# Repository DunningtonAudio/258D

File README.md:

# 258D
A dual oscillator project

The 258D Dual Oscillator is designed to replicate the functionality of the Buchla 258C module using modern construction techniques and readily available parts. Like Mark Verbos’ 258V and Dustin Stroh’s 258J, the 258D uses the exponential converter and triangle core from the Electronotes VCO option 3, designed by Bernie Hutchins, with output waveshaping derived from Don Buchla’s original 258 Design.

Additionally, the 258D includes:

* A stable voltage reference to isolate the frequency controls from fluctuations and noise on the power supply rails.
* High frequency compensation for improved tracking.
* A scaled V/O CV input in place of the original scaling potentiometer.
* The option to select either saw or square waveshapes for each oscillator by setting a jumper on the rear of the module.
* A buffered copy of the triangle core replacing the rightmost output of each oscillator.
 
There are several build options to adjust the function of the module to a particular users requirements.

The repository contains:

* KiCad project files
* Schematic and build/calibration notes as PDF files
* Bill of Materials in ODS format
* Interactive webpage for matching BOM items to PCB locations

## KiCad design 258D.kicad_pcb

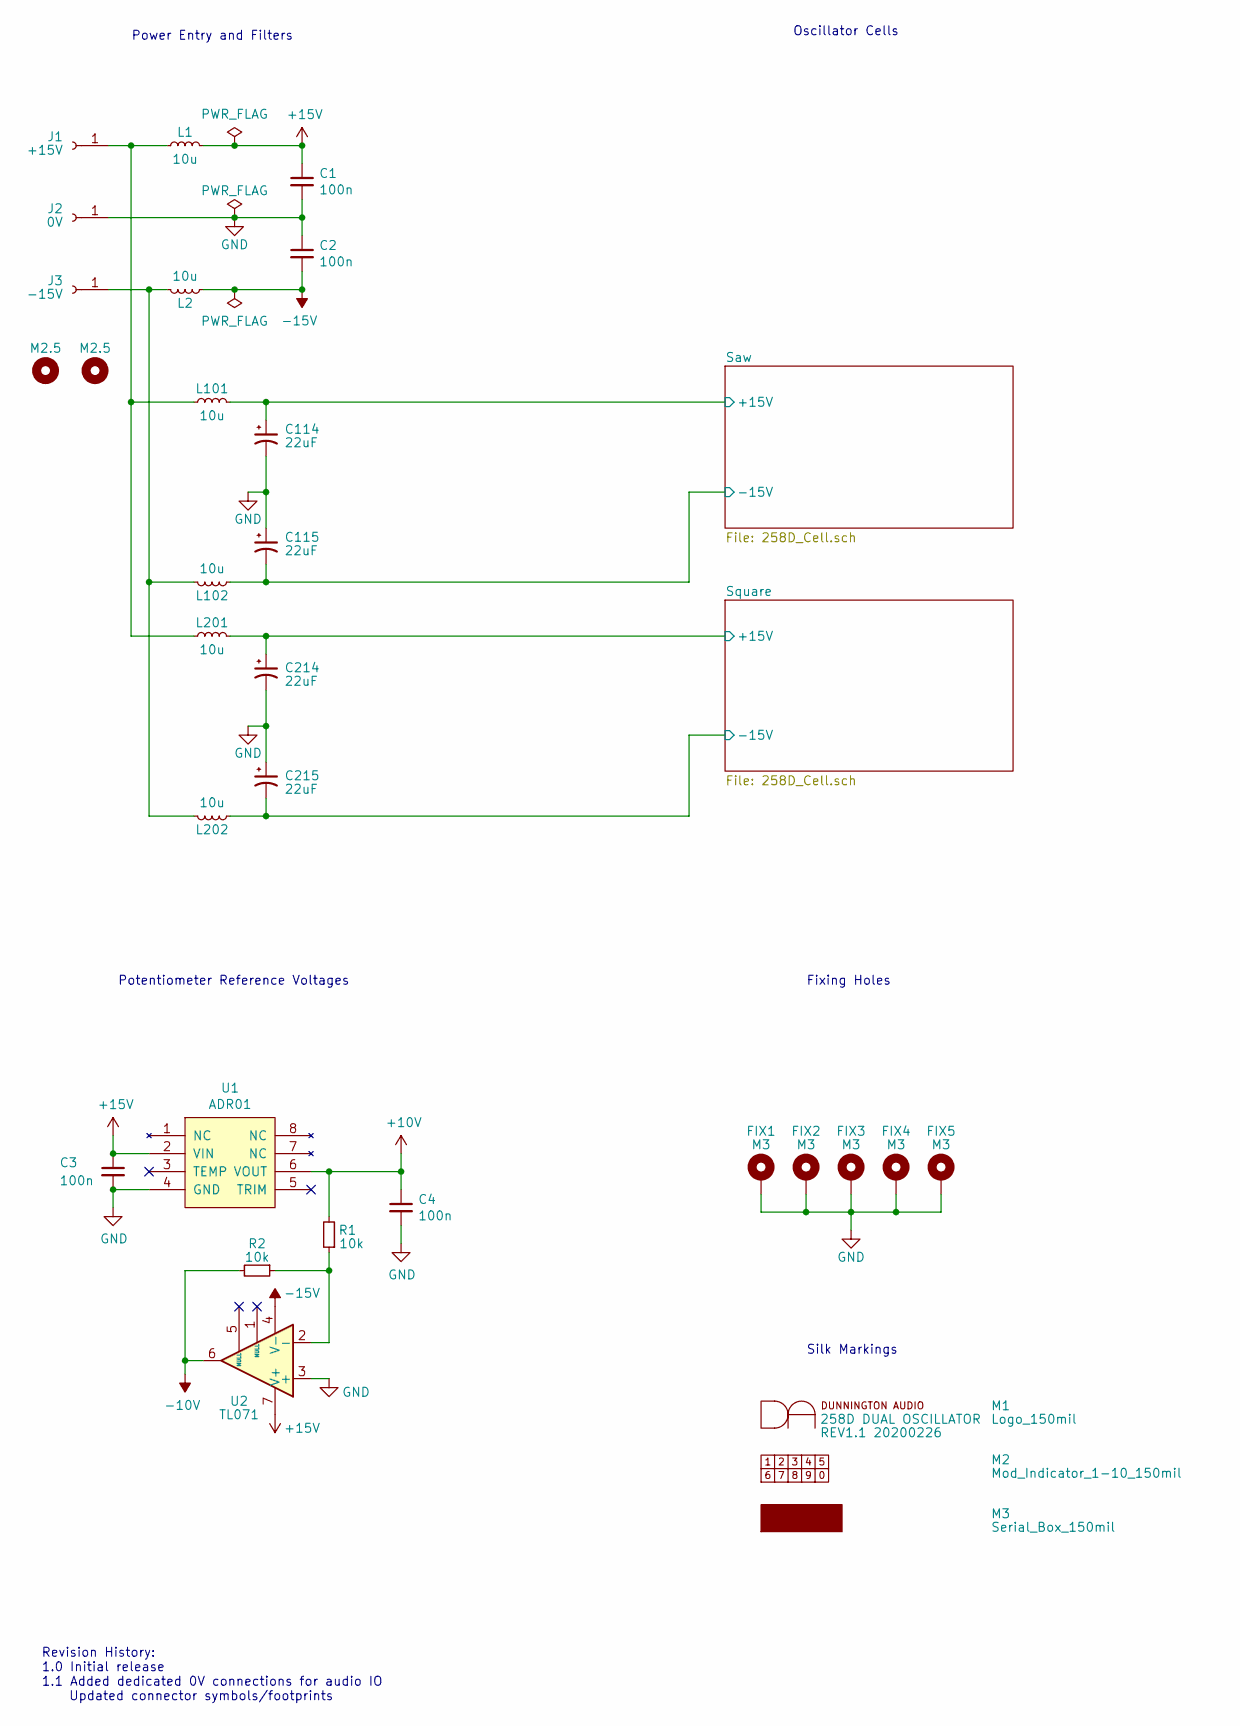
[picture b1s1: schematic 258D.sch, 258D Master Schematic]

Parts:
C1, C2, C3, C4: 100n; C_0805_2012Metric
C114, C115, C214, C215: 22uF; CP_Elec_5x5.8
FIX1, FIX2, FIX3, FIX4, FIX5: M3; MountingHole_3.2mm_M3_Pad_Via
J1: +15V; SolderWirePad_single_1-2mmDrill
J2: 0V; SolderWirePad_single_1-2mmDrill
J3: -15V; SolderWirePad_single_1-2mmDrill
L1, L2, L101, L102, L201, L202: 10u; L_0805_2012Metric; MPN LBC2012T100K
M1: Logo_150mil
M2: Mod_Indicator_1-10_150mil
M3: Serial_Box_150mil
MK101, MK102: M2.5; MountingHole_2.5mm
R1, R2: 10k; R_0805_2012Metric
U1: ADR01; SOIC-8_3.9x4.9mm_P1.27mm
U2: TL071; SOIC-8_3.9x4.9mm_P1.27mm

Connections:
+10V: C4.1, R1.2, U1.6 (VOUT); also elsewhere on the board
+15V: C1.1, C3.1, L1.2, U1.2 (VIN), U2.7 (V+)
-10V: R2.2, U2.6; also elsewhere on the board
-15V: C2.2, L2.2, U2.4 (V-)
/Saw/+15V: C114.1, L101.2; also elsewhere on the board
/Saw/-15V: C115.2, L102.2; also elsewhere on the board
/Square/+15V: C214.1, L201.2; also elsewhere on the board
/Square/-15V: C215.2, L202.2; also elsewhere on the board
GND: C1.2, C2.1, C3.2, C4.2, C114.2, C115.1, C214.2, C215.1, FIX1.1, FIX2.1, FIX3.1, FIX4.1, FIX5.1, J2.1, U1.4 (GND), U2.3 (+); also elsewhere on the board
unnamed: J1.1, L1.1, L101.1, L201.1
unnamed: J3.1, L2.1, L102.1, L202.1
unnamed: R1.1, R2.1, U2.2 (-)

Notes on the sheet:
Oscillator Cells
Fixing Holes
Potentiometer Reference Voltages
Power Entry and Filters
Revision History: 1.0 Initial release 1.1 Added dedicated 0V connections for audio IO Updated connector symbols/footprints
Silk Markings

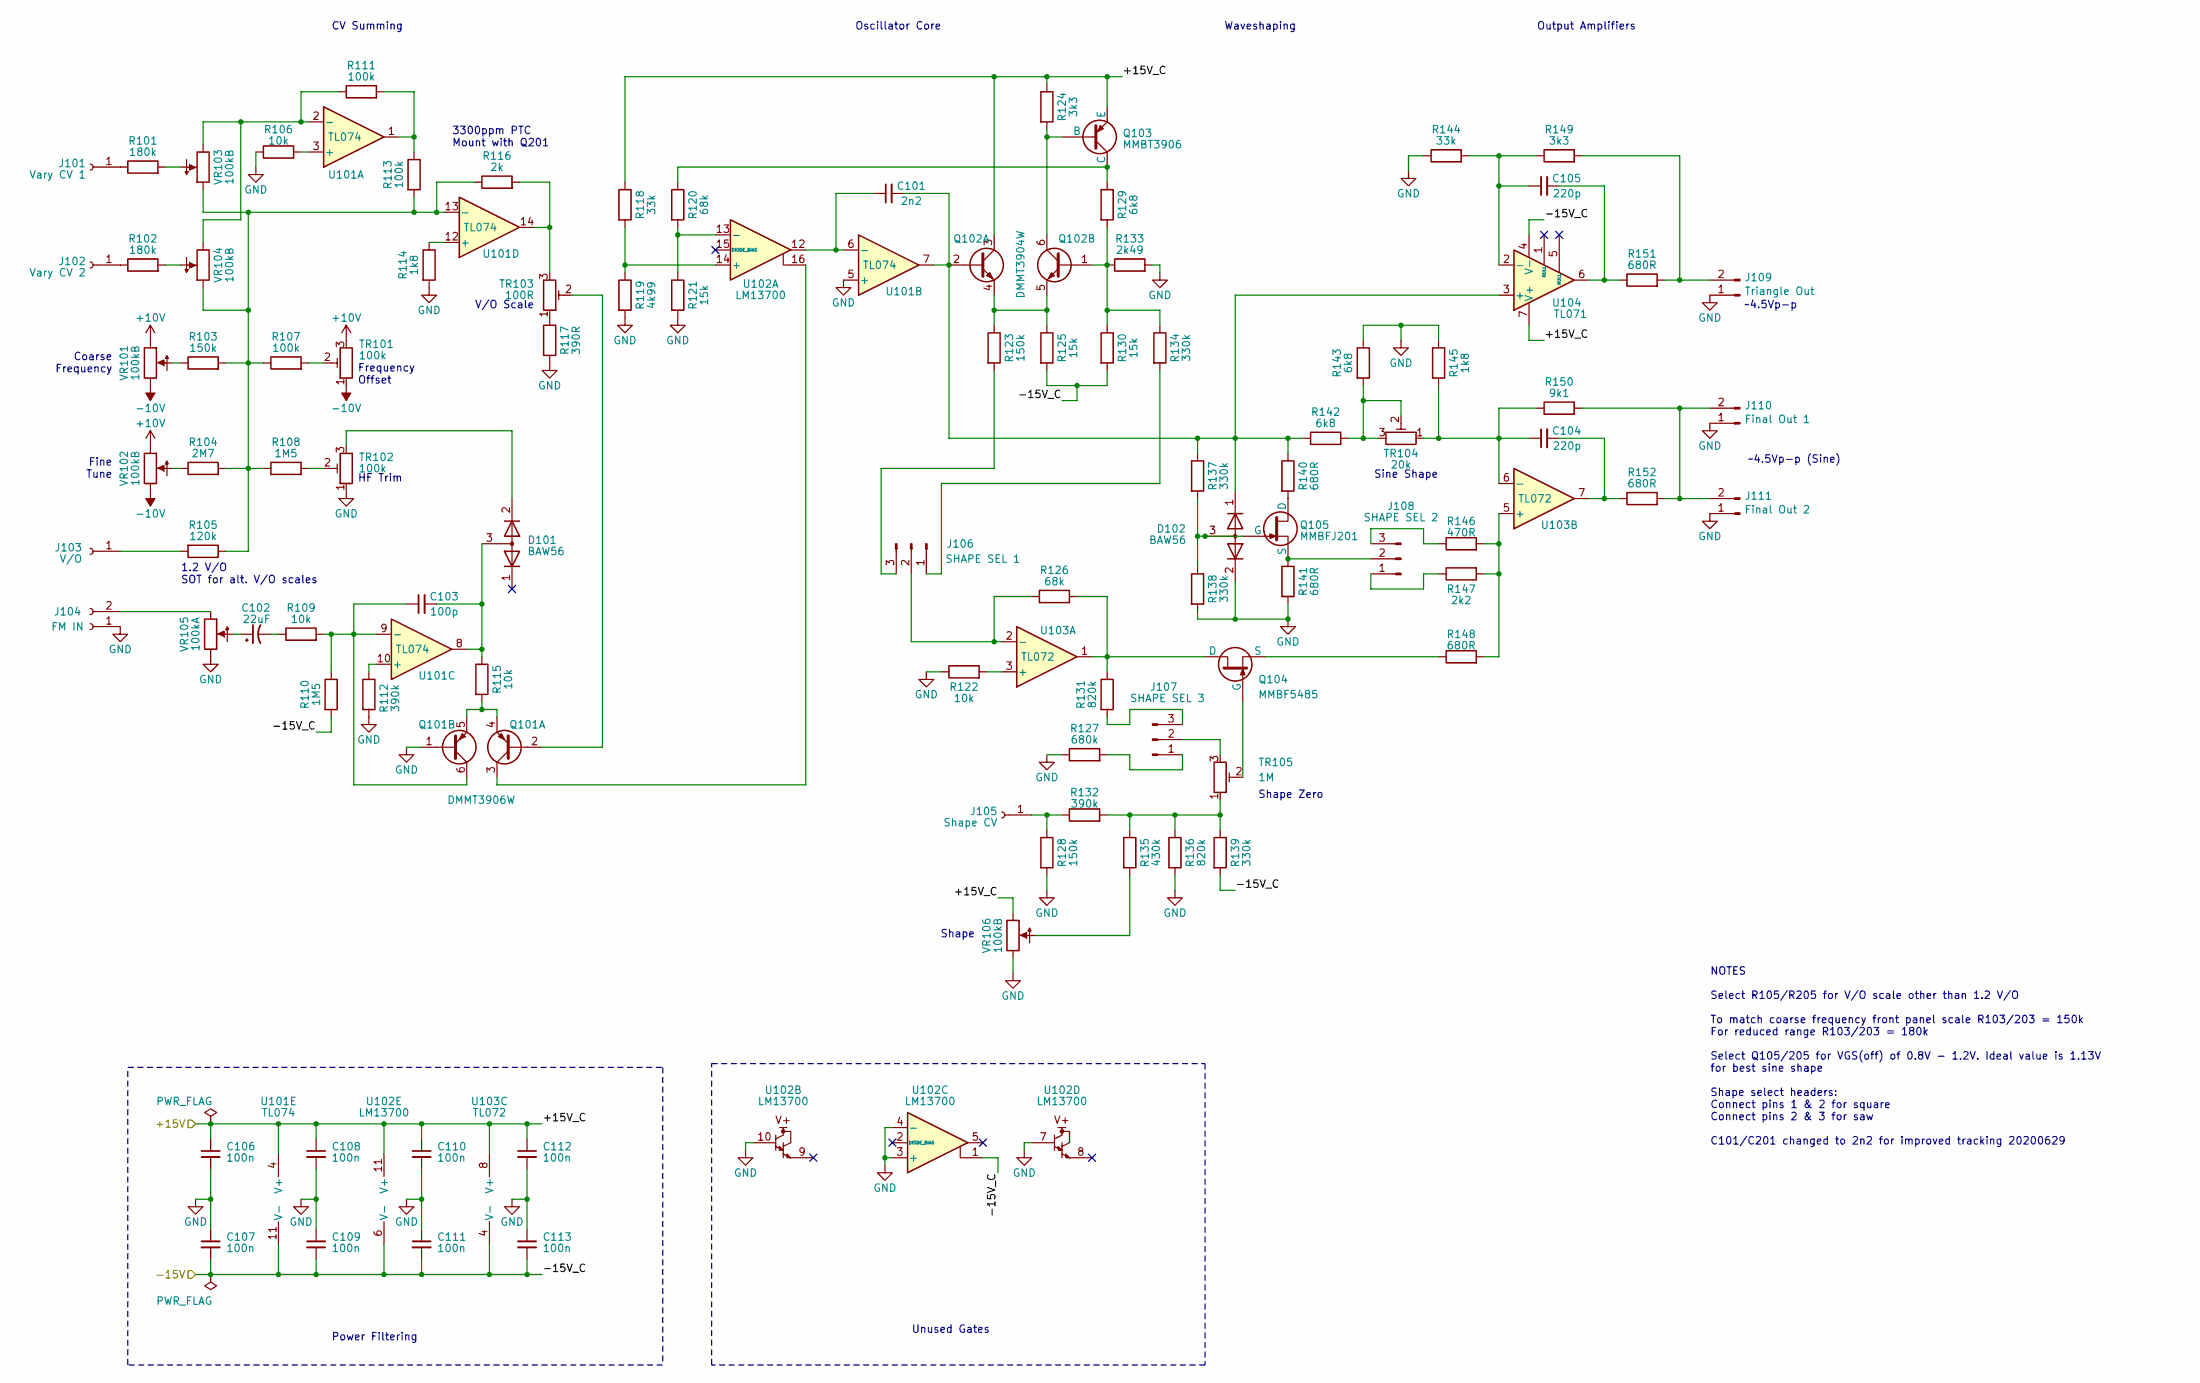
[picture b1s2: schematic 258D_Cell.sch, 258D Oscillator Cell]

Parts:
C101: 2n2; C_0805_2012Metric
C102: 22uF; CP_Elec_5x5.8
C103: 100p; C_0805_2012Metric
C104, C105: 220p; C_0805_2012Metric
C106, C107, C108, C109, C110, C111, C112, C113: 100n; C_0805_2012Metric
D101, D102: BAW56; SOT-23
J101: Vary CV 1; Johnson_108-09XX-001
J102: Vary CV 2; Johnson_108-09XX-001
J103: V/O; Johnson_108-09XX-001
J104: FM IN; Switchcraft_41
J105: Shape CV; Johnson_108-09XX-001
J106: SHAPE SEL 1; PinHeader_1x03_P2.54mm_Vertical
J107: SHAPE SEL 3; PinHeader_1x03_P2.54mm_Vertical
J108: SHAPE SEL 2; PinHeader_1x03_P2.54mm_Vertical
J109: Triangle Out; Switchcraft_41
J110: Final Out 1; Switchcraft_41
J111: Final Out 2; Switchcraft_41
Q101: DMMT3906W; SOT-363_SC-70-6
Q102: DMMT3904W; SOT-363_SC-70-6
Q103: MMBT3906; SOT-23
Q104: MMBF5485; SOT-23
Q105: MMBFJ201; SOT-23
R101, R102: 180k; R_0805_2012Metric
R103, R123, R128: 150k; R_0805_2012Metric
R104: 2M7; R_0805_2012Metric
R105: 120k; R_0805_2012Metric
R106, R109, R115, R122: 10k; R_0805_2012Metric
R107, R111, R113: 100k; R_0805_2012Metric
R108, R110: 1M5; R_0805_2012Metric
R112, R132: 390k; R_0805_2012Metric
R114, R145: 1k8; R_0805_2012Metric
R116: 2k; R_0805_2012Metric
R117: 390R; R_0805_2012Metric
R118, R144: 33k; R_0805_2012Metric
R119: 4k99; R_0805_2012Metric
R120, R126: 68k; R_0805_2012Metric
R121, R125, R130: 15k; R_0805_2012Metric
R124, R149: 3k3; R_0805_2012Metric
R127: 680k; R_0805_2012Metric
R129, R142, R143: 6k8; R_0805_2012Metric
R131, R136: 820k; R_0805_2012Metric
R133: 2k49; R_0805_2012Metric
R134, R137, R138, R139: 330k; R_0805_2012Metric
R135: 430k; R_0805_2012Metric
R140, R141, R148, R151, R152: 680R; R_0805_2012Metric
R146: 470R; R_0805_2012Metric
R147: 2k2; R_0805_2012Metric
R150: 9k1; R_0805_2012Metric
TR101, TR102: 100k; Potentiometer_Bourns_3314J_Vertical
TR103: 100R; Potentiometer_Bourns_3314J_Vertical
TR104: 20k; Potentiometer_Bourns_3314J_Vertical
TR105: 1M; Potentiometer_Bourns_3314J_Vertical
U101: TL074; SOIC-14_3.9x8.7mm_P1.27mm
U102: LM13700; SOIC-16_3.9x9.9mm_P1.27mm
U103: TL072; SOIC-8_3.9x4.9mm_P1.27mm
U104: TL071; SOIC-8_3.9x4.9mm_P1.27mm
VR101, VR103, VR104, VR106: 100kB; RV16AF-41-(L)R1-XXX
VR102: 100kB; RD901F-40-00D
VR105: 100kA; RV16AF-41-(L)R1-XXX

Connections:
+10V: TR101.3, VR101.3 (1), VR102.3 (1); also elsewhere on the board
-10V: TR101.1, VR101.1 (3), VR102.1 (3); also elsewhere on the board
/Saw/+15V: C106.1, C108.1, C110.1, C112.1, Q102.3 (C1), Q103.2 (E), R118.1, R124.1, U101.4 (V+), U102.11 (V+), U103.8 (V+), U104.7 (V+), VR106.3 (1); also elsewhere on the board
/Saw/-15V: C107.2, C109.2, C111.2, C113.2, R110.2, R125.2, R130.2, R139.2, U101.11 (V-), U102.1, U102.6 (V-), U103.4 (V-), U104.4 (V-); also elsewhere on the board
GND: C106.2, C107.1, C108.2, C109.1, C110.2, C111.1, C112.2, C113.1, D102.2 (K), J104.1, J109.1, J110.1, J111.1, Q101.1 (B2), R106.1, R112.2, R114.2, R117.2, R119.2, R121.2, R122.1, R127.1, R128.2, R133.2, R136.2, R138.2, R141.2, R143.1, R144.1, R145.1, TR102.1, U101.5 (+), U102.3 (+), U102.4 (-), U102.7, U102.10, VR105.1 (3), VR106.1 (3); also elsewhere on the board
unnamed: C101.1, U101.6 (-), U102.12
unnamed: C101.2, D102.1 (K), Q102.2 (B1), R137.1, R140.1, R142.1, U101.7, U104.3 (+)
unnamed: C102.1, VR105.2
unnamed: C102.2, R109.1
unnamed: C103.1, Q101.6 (C2), R109.2, R110.1, U101.9 (-)
unnamed: C103.2, D101.3 (A), R115.1, U101.8
unnamed: C104.1, R145.2, R150.1, TR104.1, U103.6 (-)
unnamed: C104.2, R152.1, U103.7
unnamed: C105.1, R144.2, R149.1, U104.2 (-)
unnamed: C105.2, R151.1, U104.6
unnamed: D101.2 (K), TR102.3
unnamed: D102.3 (A), Q105.3 (G), R137.2, R138.1
unnamed: J101.1, R101.1
unnamed: J102.1, R102.1
unnamed: J103.1, R105.2
unnamed: J104.2, VR105.3 (1)
unnamed: J105.1, R128.1, R132.1
unnamed: J106.1, R134.2
unnamed: J106.2, R126.1, U103.2 (-)
unnamed: J106.3, R123.2
unnamed: J107.1, R127.2
unnamed: J107.2, TR105.3
unnamed: J107.3, R131.2
unnamed: J108.1, R147.1
unnamed: J108.2, Q105.2 (S), R141.1
unnamed: J108.3, R146.1
unnamed: J109.2, R149.2, R151.2
unnamed: J110.2, J111.2, R150.2, R152.2
unnamed: Q101.2 (B1), TR103.2
unnamed: Q101.3 (C1), U102.16
unnamed: Q101.4 (E1), Q101.5 (E2), R115.2
unnamed: Q102.1 (B2), R129.2, R130.1, R133.1, R134.1
unnamed: Q102.4 (E1), Q102.5 (E2), R123.1, R125.1
unnamed: Q102.6 (C2), Q103.1 (B), R124.2
unnamed: Q103.3 (C), R120.1, R129.1
unnamed: Q104.1 (D), R126.2, R131.1, U103.1
unnamed: Q104.2 (S), R148.1
unnamed: Q104.3 (G), TR105.2
unnamed: Q105.1 (D), R140.2
unnamed: R101.2, VR103.2
unnamed: R102.2, VR104.2
unnamed: R103.1, VR101.2
unnamed: R103.2, R104.2, R105.1, R107.1, R108.1, R113.2, R116.1, U101.13 (-), VR103.3 (1), VR104.3 (1)
unnamed: R104.1, VR102.2
unnamed: R106.2, U101.3 (+)
unnamed: R107.2, TR101.2
unnamed: R108.2, TR102.2
unnamed: R111.1, U101.2 (-), VR103.1 (3), VR104.1 (3)
unnamed: R111.2, R113.1, U101.1
unnamed: R112.1, U101.10 (+)
unnamed: R114.1, U101.12 (+)
unnamed: R116.2, TR103.3, U101.14
unnamed: R117.1, TR103.1
unnamed: R118.2, R119.1, U102.14 (+)
unnamed: R120.2, R121.1, U102.13 (-)
unnamed: R122.2, U103.3 (+)
unnamed: R132.2, R135.1, R136.1, R139.1, TR105.1
unnamed: R135.2, VR106.2
unnamed: R142.2, R143.2, TR104.2, TR104.3
unnamed: R146.2, R147.2, R148.2, U103.5 (+)

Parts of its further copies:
C201: 2n2; C_0805_2012Metric
C202: 22uF; CP_Elec_5x5.8
C203: 100p; C_0805_2012Metric
C204, C205: 220p; C_0805_2012Metric
C206, C207, C208, C209, C210, C211, C212, C213: 100n; C_0805_2012Metric
D201, D202: BAW56; SOT-23
J201: Vary CV 1; Johnson_108-09XX-001
J202: Vary CV 2; Johnson_108-09XX-001
J203: V/O; Johnson_108-09XX-001
J204: FM IN; Switchcraft_41
J205: Shape CV; Johnson_108-09XX-001
J206: SHAPE SEL 1; PinHeader_1x03_P2.54mm_Vertical
J207: SHAPE SEL 3; PinHeader_1x03_P2.54mm_Vertical
J208: SHAPE SEL 2; PinHeader_1x03_P2.54mm_Vertical
J209: Triangle Out; Switchcraft_41
J210: Final Out 1; Switchcraft_41
J211: Final Out 2; Switchcraft_41
Q201: DMMT3906W; SOT-363_SC-70-6
Q202: DMMT3904W; SOT-363_SC-70-6
Q203: MMBT3906; SOT-23
Q204: MMBF5485; SOT-23
Q205: MMBFJ201; SOT-23
R201, R202: 180k; R_0805_2012Metric
R203, R223, R228: 150k; R_0805_2012Metric
R204: 2M7; R_0805_2012Metric
R205: 120k; R_0805_2012Metric
R206, R209, R215, R222: 10k; R_0805_2012Metric
R207, R211, R213: 100k; R_0805_2012Metric
R208, R210: 1M5; R_0805_2012Metric
R212, R232: 390k; R_0805_2012Metric
R214, R245: 1k8; R_0805_2012Metric
R216: 2k; R_0805_2012Metric
R217: 390R; R_0805_2012Metric
R218, R244: 33k; R_0805_2012Metric
R219: 4k99; R_0805_2012Metric
R220, R226: 68k; R_0805_2012Metric
R221, R225, R230: 15k; R_0805_2012Metric
R224, R249: 3k3; R_0805_2012Metric
R227: 680k; R_0805_2012Metric
R229, R242, R243: 6k8; R_0805_2012Metric
R231, R236: 820k; R_0805_2012Metric
R233: 2k49; R_0805_2012Metric
R234, R237, R238, R239: 330k; R_0805_2012Metric
R235: 430k; R_0805_2012Metric
R240, R241, R248, R251, R252: 680R; R_0805_2012Metric
R246: 470R; R_0805_2012Metric
R247: 2k2; R_0805_2012Metric
R250: 9k1; R_0805_2012Metric
TR201, TR202: 100k; Potentiometer_Bourns_3314J_Vertical
TR203: 100R; Potentiometer_Bourns_3314J_Vertical
TR204: 20k; Potentiometer_Bourns_3314J_Vertical
TR205: 1M; Potentiometer_Bourns_3314J_Vertical
U201: TL074; SOIC-14_3.9x8.7mm_P1.27mm
U202: LM13700; SOIC-16_3.9x9.9mm_P1.27mm
U203: TL072; SOIC-8_3.9x4.9mm_P1.27mm
U204: TL071; SOIC-8_3.9x4.9mm_P1.27mm
VR201, VR203, VR204, VR206: 100kB; RV16AF-41-(L)R1-XXX
VR202: 100kB; RD901F-40-00D
VR205: 100kA; RV16AF-41-(L)R1-XXX

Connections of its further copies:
+10V: TR201.3, VR201.3 (1), VR202.3 (1); also elsewhere on the board
-10V: TR201.1, VR201.1 (3), VR202.1 (3); also elsewhere on the board
/Square/+15V: C206.1, C208.1, C210.1, C212.1, Q202.3 (C1), Q203.2 (E), R218.1, R224.1, U201.4 (V+), U202.11 (V+), U203.8 (V+), U204.7 (V+), VR206.3 (1); also elsewhere on the board
/Square/-15V: C207.2, C209.2, C211.2, C213.2, R210.2, R225.2, R230.2, R239.2, U201.11 (V-), U202.1, U202.6 (V-), U203.4 (V-), U204.4 (V-); also elsewhere on the board
GND: C206.2, C207.1, C208.2, C209.1, C210.2, C211.1, C212.2, C213.1, D202.2 (K), J204.1, J209.1, J210.1, J211.1, Q201.1 (B2), R206.1, R212.2, R214.2, R217.2, R219.2, R221.2, R222.1, R227.1, R228.2, R233.2, R236.2, R238.2, R241.2, R243.1, R244.1, R245.1, TR202.1, U201.5 (+), U202.3 (+), U202.4 (-), U202.7, U202.10, VR205.1 (3), VR206.1 (3); also elsewhere on the board
unnamed: C201.1, U201.6 (-), U202.12
unnamed: C201.2, D202.1 (K), Q202.2 (B1), R237.1, R240.1, R242.1, U201.7, U204.3 (+)
unnamed: C202.1, VR205.2
unnamed: C202.2, R209.1
unnamed: C203.1, Q201.6 (C2), R209.2, R210.1, U201.9 (-)
unnamed: C203.2, D201.3 (A), R215.1, U201.8
unnamed: C204.1, R245.2, R250.1, TR204.1, U203.6 (-)
unnamed: C204.2, R252.1, U203.7
unnamed: C205.1, R244.2, R249.1, U204.2 (-)
unnamed: C205.2, R251.1, U204.6
unnamed: D201.2 (K), TR202.3
unnamed: D202.3 (A), Q205.3 (G), R237.2, R238.1
unnamed: J201.1, R201.1
unnamed: J202.1, R202.1
unnamed: J203.1, R205.2
unnamed: J204.2, VR205.3 (1)
unnamed: J205.1, R228.1, R232.1
unnamed: J206.1, R234.2
unnamed: J206.2, R226.1, U203.2 (-)
unnamed: J206.3, R223.2
unnamed: J207.1, R227.2
unnamed: J207.2, TR205.3
unnamed: J207.3, R231.2
unnamed: J208.1, R247.1
unnamed: J208.2, Q205.2 (S), R241.1
unnamed: J208.3, R246.1
unnamed: J209.2, R249.2, R251.2
unnamed: J210.2, J211.2, R250.2, R252.2
unnamed: Q201.2 (B1), TR203.2
unnamed: Q201.3 (C1), U202.16
unnamed: Q201.4 (E1), Q201.5 (E2), R215.2
unnamed: Q202.1 (B2), R229.2, R230.1, R233.1, R234.1
unnamed: Q202.4 (E1), Q202.5 (E2), R223.1, R225.1
unnamed: Q202.6 (C2), Q203.1 (B), R224.2
unnamed: Q203.3 (C), R220.1, R229.1
unnamed: Q204.1 (D), R226.2, R231.1, U203.1
unnamed: Q204.2 (S), R248.1
unnamed: Q204.3 (G), TR205.2
unnamed: Q205.1 (D), R240.2
unnamed: R201.2, VR203.2
unnamed: R202.2, VR204.2
unnamed: R203.1, VR201.2
unnamed: R203.2, R204.2, R205.1, R207.1, R208.1, R213.2, R216.1, U201.13 (-), VR203.3 (1), VR204.3 (1)
unnamed: R204.1, VR202.2
unnamed: R206.2, U201.3 (+)
unnamed: R207.2, TR201.2
unnamed: R208.2, TR202.2
unnamed: R211.1, U201.2 (-), VR203.1 (3), VR204.1 (3)
unnamed: R211.2, R213.1, U201.1
unnamed: R212.1, U201.10 (+)
unnamed: R214.1, U201.12 (+)
unnamed: R216.2, TR203.3, U201.14
unnamed: R217.1, TR203.1
unnamed: R218.2, R219.1, U202.14 (+)
unnamed: R220.2, R221.1, U202.13 (-)
unnamed: R222.2, U203.3 (+)
unnamed: R232.2, R235.1, R236.1, R239.1, TR205.1
unnamed: R235.2, VR206.2
unnamed: R242.2, R243.2, TR204.2, TR204.3
unnamed: R246.2, R247.2, R248.2, U203.5 (+)

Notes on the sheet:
3300ppm PTC Mount with Q201
Coarse Frequency
Fine Tune
Sine Shape
Shape Zero
HF Trim
Frequency Offset
V/O Scale
Unused Gates
Power Filtering
CV Summing
Oscillator Core
Waveshaping
Output Amplifiers
Shape
1.2 V/O SOT for alt. V/O scales
~~4.5Vp-p
~~4.5Vp-p (Sine)
NOTES Select R105/R205 for V/O scale other than 1.2 V/O To match coarse frequency front panel scale R103/203 = 150k For reduced range R103/203 = 180k Select Q105/205 for VGS(off) of 0.8V - 1.2V. Ideal value is 1.13V for best sine shape Shape select headers: Connect pins 1 & 2 for square Connect pin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

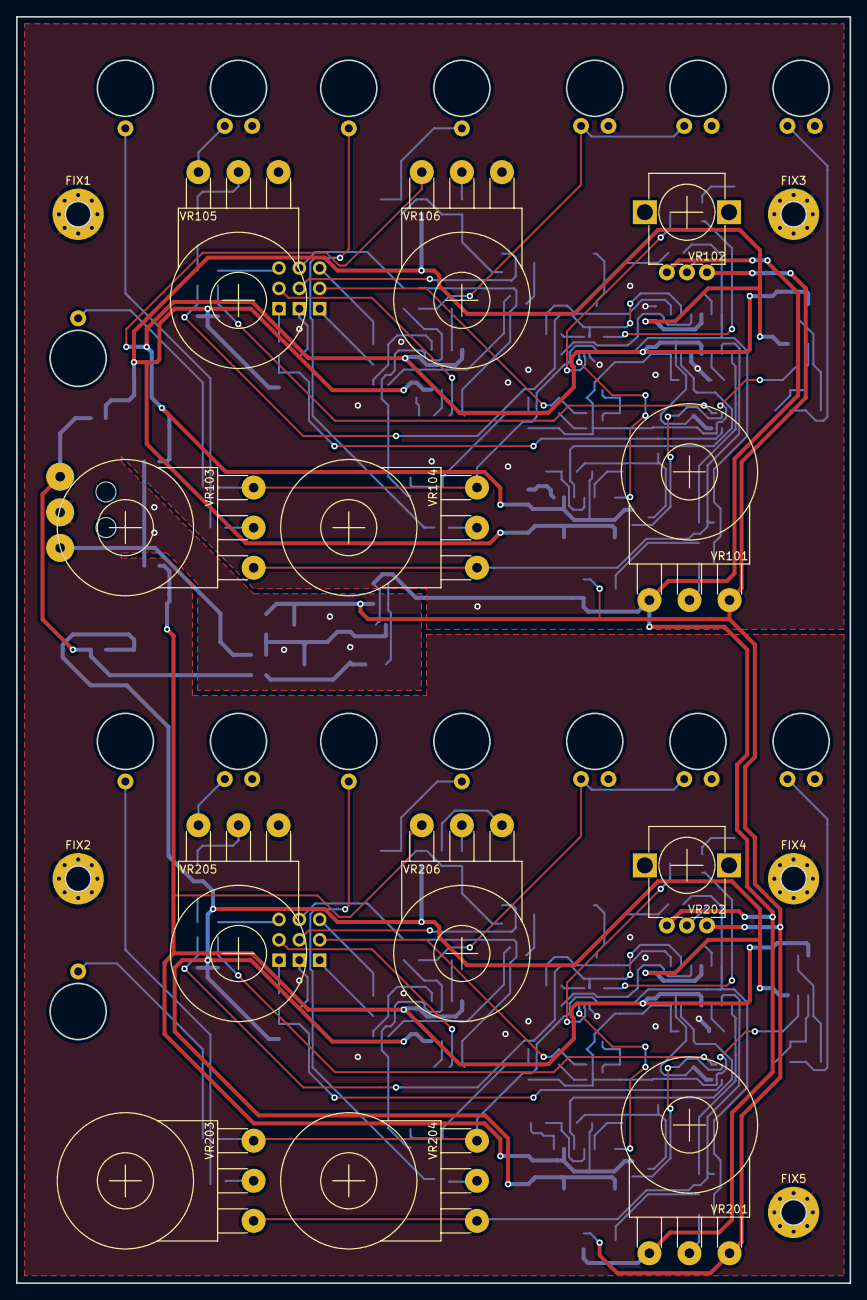
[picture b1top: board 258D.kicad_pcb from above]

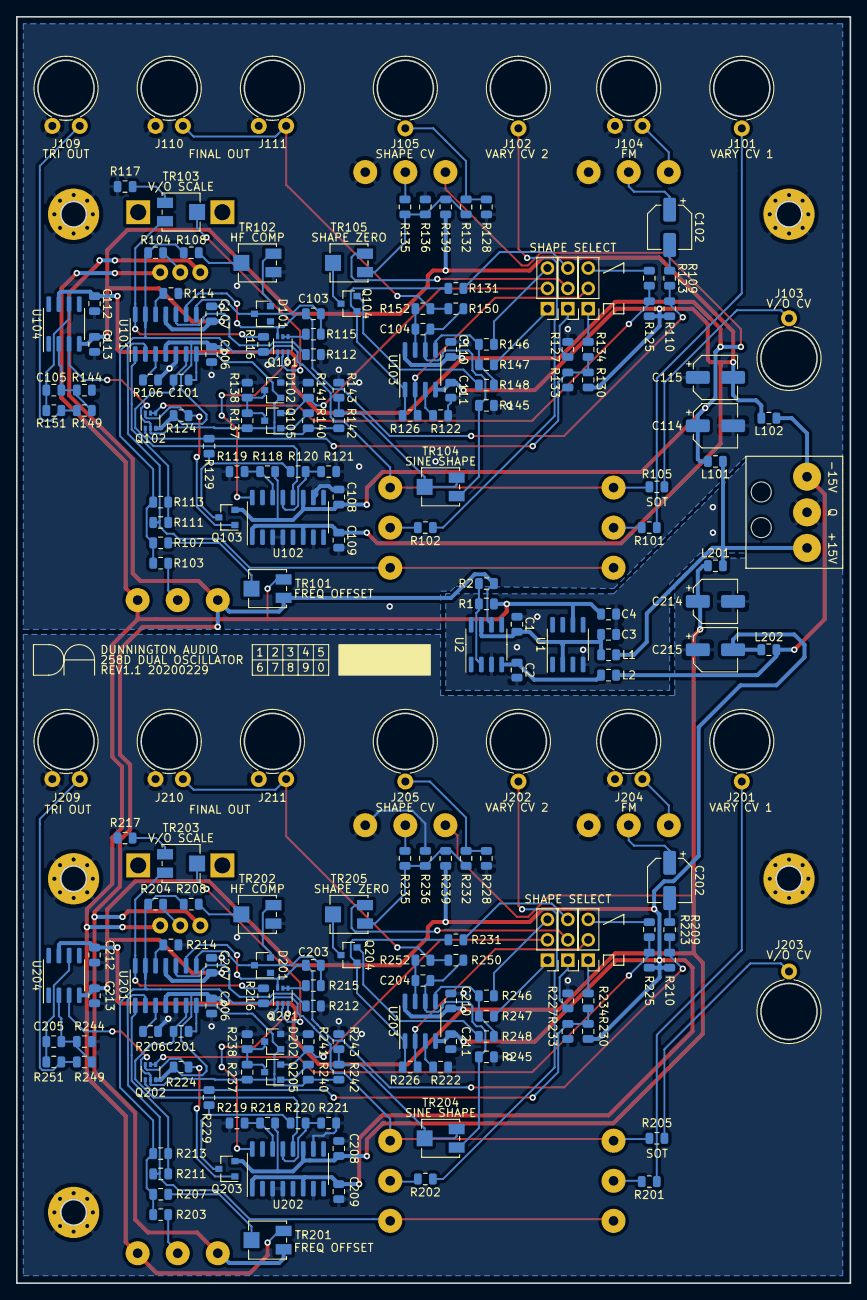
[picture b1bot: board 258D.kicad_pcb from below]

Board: 2 copper layers, 104.0 x 158.0 mm, 227 parts (210 on the bottom side), 132 nets.

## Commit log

2020-05-13 Add .gitignore
2020-05-19 Update .gitignore, update BOM, add BOM pdf.
2020-06-10 Update BOM, BOM pdf, notes.
2020-06-29 Update BOM, BOM pdf, notes, schematic
2020-08-21 Update BOM, BOM pdf
2020-11-13 Update Q104/204 value in schematic, board, BOM, iBOM, clarify selection criteria for Q105/205 in schematic, BOM, notes.
